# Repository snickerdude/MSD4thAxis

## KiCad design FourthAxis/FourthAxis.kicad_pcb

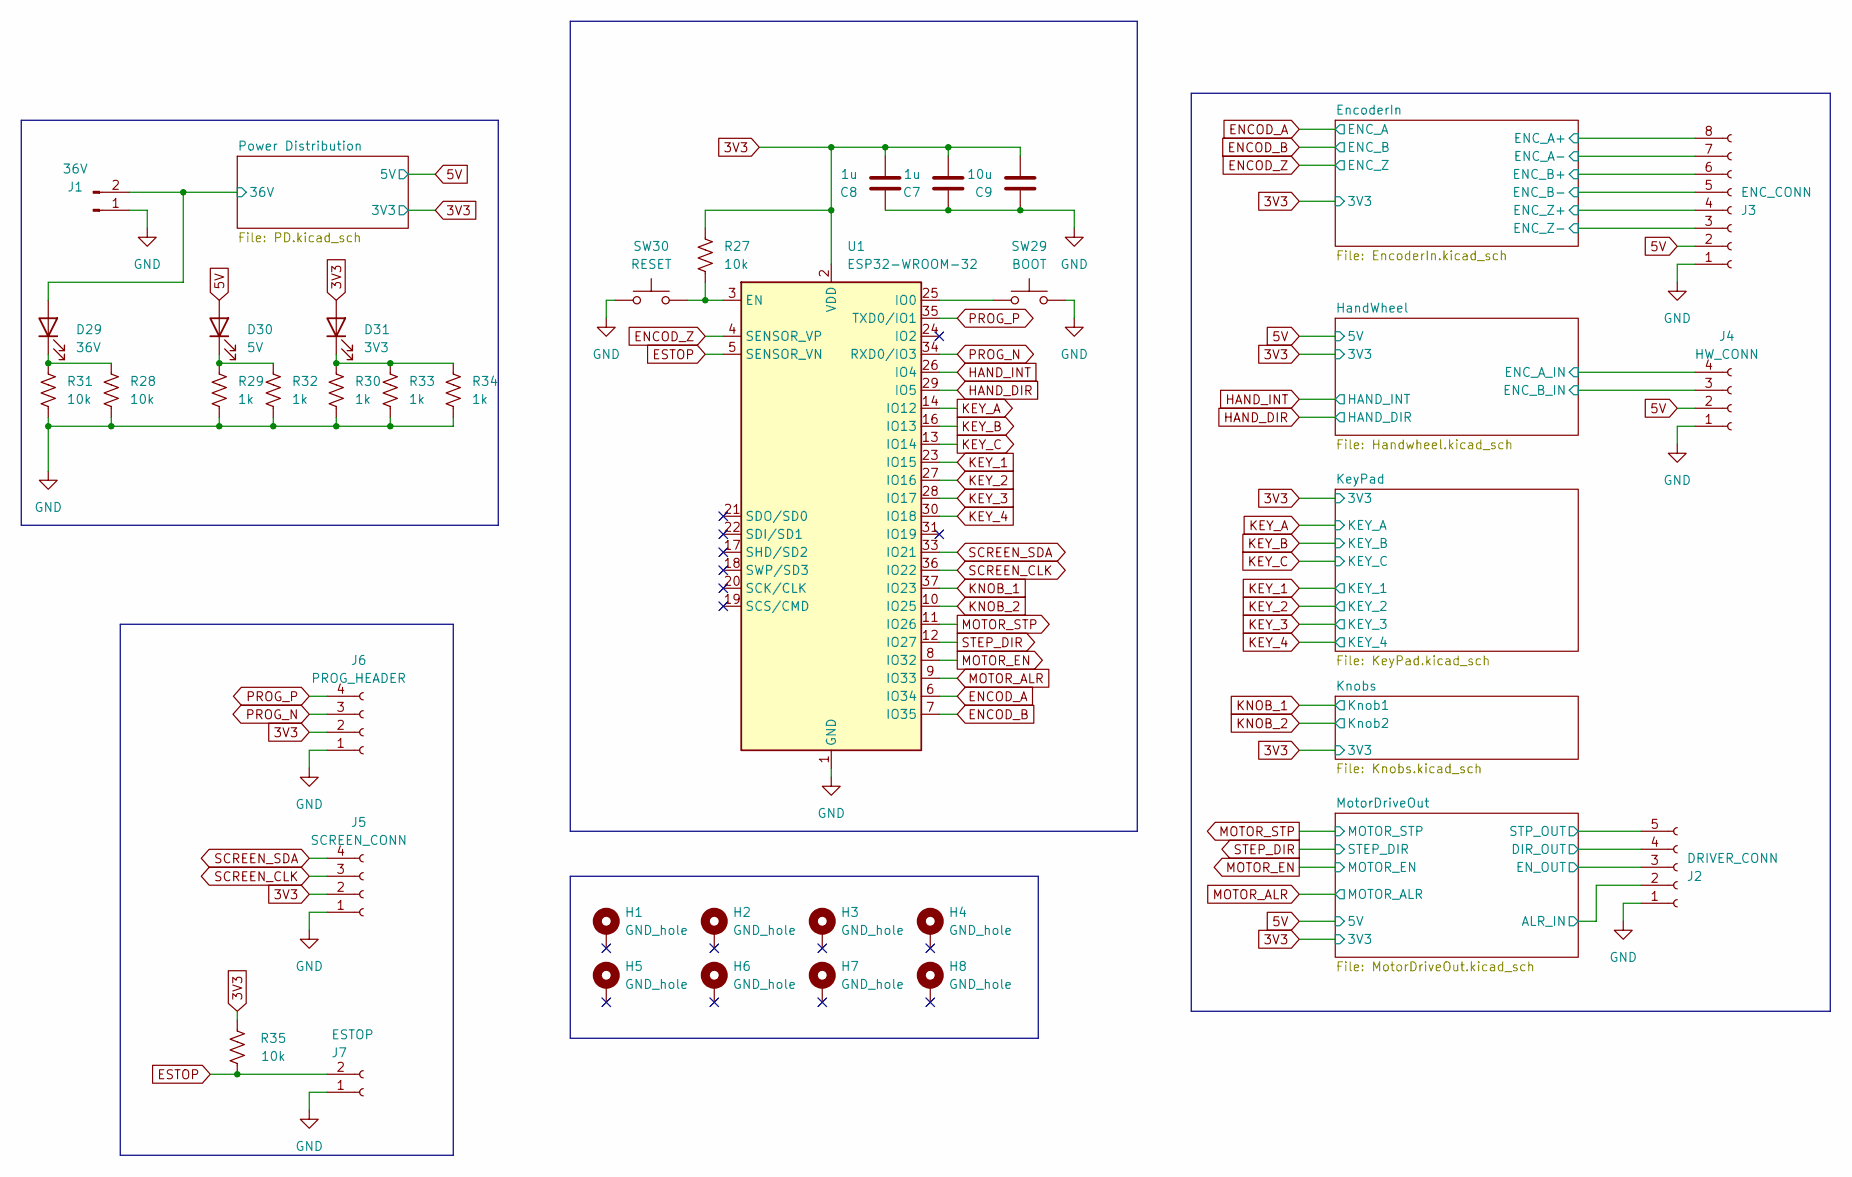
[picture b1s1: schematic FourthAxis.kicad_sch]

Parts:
C7, C8: 1u; C_0603_1608Metric; digikey 1276-1184-1-ND
C9: 10u; C_0603_1608Metric; digikey 1292-0603X106M100CT-ND
D29: 36V; LED_0603_1608Metric; digikey 160-1182-1-ND
D30: 5V; LED_0603_1608Metric; digikey 160-1182-1-ND
D31: 3V3; LED_0603_1608Metric; digikey 160-1182-1-ND
H1, H2, H3, H4, H5, H6, H7, H8: GND_hole; MountingHole_2.2mm_M2_Pad
J1: 36V; PinHeader_1x02_P2.54mm_Vertical
J2: DRIVER_CONN; PinHeader_1x05_P2.54mm_Vertical
J3: ENC_CONN; PinHeader_1x08_P2.54mm_Vertical
J4: HW_CONN; PinHeader_1x04_P2.54mm_Vertical
J5: SCREEN_CONN; PinHeader_1x04_P2.54mm_Vertical
J6: PROG_HEADER; PinHeader_1x04_P2.54mm_Vertical
J7: ESTOP; PinHeader_1x02_P2.54mm_Vertical
R27, R28, R31, R35: 10k; R_0603_1608Metric; digikey 311-10.0KHRCT-ND
R29, R30, R32, R33, R34: 1k; R_0603_1608Metric; digikey 311-1.00KHRCT-ND
SW29: BOOT; SW_Push_1P1T_NO_CK_KMR2; digikey CKN10284CT-ND
SW30: RESET; SW_Push_1P1T_NO_CK_KMR2; digikey CKN10284CT-ND
U1: ESP32-WROOM-32; Digikey Part Number 1965-ESP32-WROOM-32E-N4CT-ND

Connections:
3V3: C7.2, C8.2, C9.2, D31.2 (A), J5.2, J6.2, R27.1, R35.1, U1.2 (VDD); also elsewhere on the board
5V: D30.2 (A), J3.2, J4.2; also elsewhere on the board
/EncoderIn/ENC_A+: J3.8; also elsewhere on the board
/EncoderIn/ENC_A-: J3.7; also elsewhere on the board
/EncoderIn/ENC_B+: J3.6; also elsewhere on the board
/EncoderIn/ENC_B-: J3.5; also elsewhere on the board
/EncoderIn/ENC_Z+: J3.4; also elsewhere on the board
/EncoderIn/ENC_Z-: J3.3; also elsewhere on the board
/HandWheel/ENC_A_IN: J4.4; also elsewhere on the board
/HandWheel/ENC_B_IN: J4.3; also elsewhere on the board
/MotorDriveOut/ALR_IN: J2.2; also elsewhere on the board
/MotorDriveOut/DIR_OUT: J2.4; also elsewhere on the board
/MotorDriveOut/EN_OUT: J2.3; also elsewhere on the board
/MotorDriveOut/STP_OUT: J2.5; also elsewhere on the board
/Power Distribution/36V: D29.2 (A), J1.2; also elsewhere on the board
ENCOD_A: U1.6 (IO34); also elsewhere on the board
ENCOD_B: U1.7 (IO35); also elsewhere on the board
ENCOD_Z: U1.4 (SENSOR_VP); also elsewhere on the board
ESTOP: J7.2, R35.2, U1.5 (SENSOR_VN)
GND: C7.1, C8.1, C9.1, J1.1, J2.1, J3.1, J4.1, J5.1, J6.1, J7.1, R28.2, R29.2, R30.2, R31.2, R32.2, R33.2, R34.2, SW29.2, SW30.2, U1.1 (GND), U1.15 (GND), U1.38 (GND), U1.39 (GND); also elsewhere on the board
HAND_DIR: U1.29 (IO5); also elsewhere on the board
HAND_INT: U1.26 (IO4); also elsewhere on the board
KEY_1: U1.23 (IO15); also elsewhere on the board
KEY_2: U1.27 (IO16); also elsewhere on the board
KEY_3: U1.28 (IO17); also elsewhere on the board
KEY_4: U1.30 (IO18); also elsewhere on the board
KEY_A: U1.14 (IO12); also elsewhere on the board
KEY_B: U1.16 (IO13); also elsewhere on the board
KEY_C: U1.13 (IO14); also elsewhere on the board
KNOB_1: U1.37 (IO23); also elsewhere on the board
KNOB_2: U1.10 (IO25); also elsewhere on the board
MOTOR_ALR: U1.9 (IO33); also elsewhere on the board
MOTOR_EN: U1.8 (IO32); also elsewhere on the board
MOTOR_STP: U1.11 (IO26); also elsewhere on the board
unnamed: D29.1 (K), R28.1, R31.1
unnamed: D30.1 (K), R29.1, R32.1
unnamed: D31.1 (K), R30.1, R33.1, R34.1
unnamed: R27.2, SW30.1, U1.3 (EN)
unnamed: SW29.1, U1.25 (IO0)
PROG_N: J6.3, U1.34 (RXD0/IO3)
PROG_P: J6.4, U1.35 (TXD0/IO1)
SCREEN_CLK: J5.3, U1.36 (IO22)
SCREEN_SDA: J5.4, U1.33 (IO21)
STEP_DIR: U1.12 (IO27); also elsewhere on the board

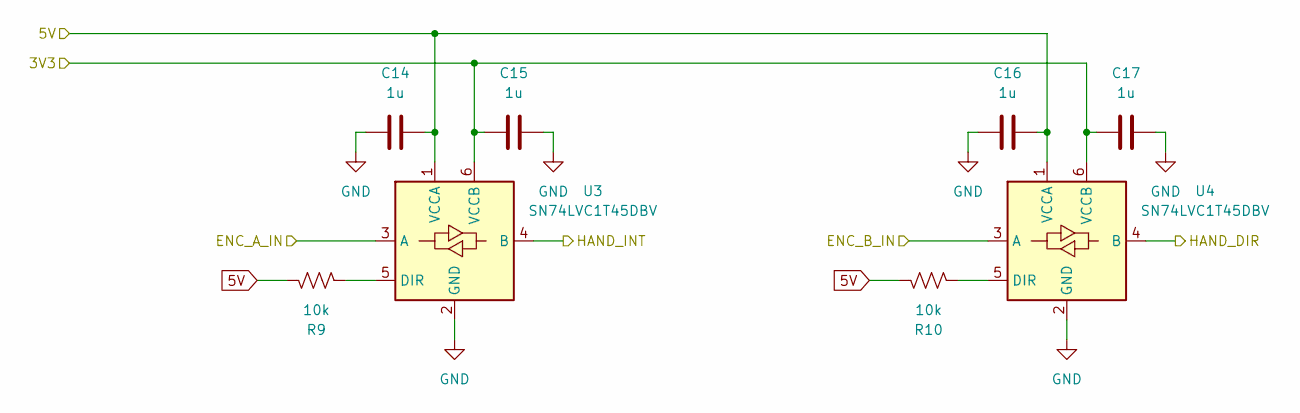
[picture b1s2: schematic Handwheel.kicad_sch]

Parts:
C14, C15, C16, C17: 1u; C_0603_1608Metric; digikey 1276-1184-1-ND
R9, R10: 10k; R_0603_1608Metric; digikey 311-10.0KHRCT-ND
U3, U4: SN74LVC1T45DBV; SOT-23-6; digikey 296-16843-1-ND

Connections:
3V3: C15.2, C17.2, U3.6 (VCCB), U4.6 (VCCB); also elsewhere on the board
5V: C14.1, C16.1, R9.1, R10.1, U3.1 (VCCA), U4.1 (VCCA); also elsewhere on the board
/HandWheel/ENC_A_IN: U3.3 (A); also elsewhere on the board
/HandWheel/ENC_B_IN: U4.3 (A); also elsewhere on the board
GND: C14.2, C15.1, C16.2, C17.1, U3.2 (GND), U4.2 (GND); also elsewhere on the board
HAND_DIR: U4.4 (B); also elsewhere on the board
HAND_INT: U3.4 (B); also elsewhere on the board
unnamed: R9.2, U3.5 (DIR)
unnamed: R10.2, U4.5 (DIR)

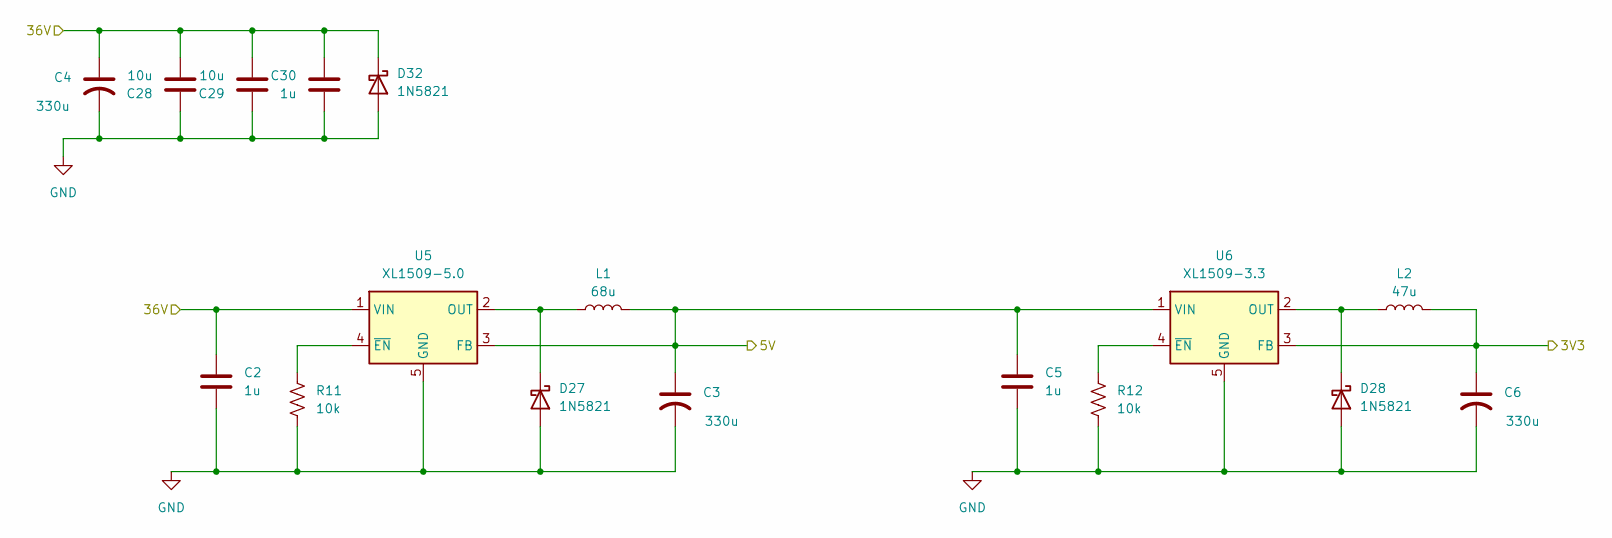
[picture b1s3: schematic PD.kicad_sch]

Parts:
C2, C5, C30: 1u; C_0603_1608Metric; digikey 1276-1184-1-ND
C3, C4, C6: 330u; CP_Elec_6.3x7.7; digikey 493-2157-1-ND
C28, C29: 10u; C_0603_1608Metric; digikey 1292-0603X106M100CT-ND
D27, D28, D32: 1N5821; D_SOD-123; digikey 641-1458-1-ND
L1: 68u; L_12x12mm_H6mm; digikey 399-MPXV1D1250L680CT-ND
L2: 47u; L_12x12mm_H6mm; digikey 399-MPXV1D1250L470CT-ND
R11, R12: 10k; R_0603_1608Metric; digikey 311-10.0KHRCT-ND
U5: XL1509-5.0; SOIC-8_3.9x4.9mm_P1.27mm; digikey 4518-XL1509-5.0CT-ND
U6: XL1509-3.3; SOIC-8_3.9x4.9mm_P1.27mm; digikey 4518-XL1509-3.3CT-ND

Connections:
3V3: C6.1, L2.2, U6.3 (FB); also elsewhere on the board
5V: C3.1, C5.1, L1.2, U5.3 (FB), U6.1 (VIN); also elsewhere on the board
/Power Distribution/36V: C2.1, C4.1, C28.2, C29.2, C30.1, D32.1 (K), U5.1 (VIN); also elsewhere on the board
GND: C2.2, C3.2, C4.2, C5.2, C6.2, C28.1, C29.1, C30.2, D27.2 (A), D28.2 (A), D32.2 (A), R11.2, R12.2, U5.5 (GND), U5.6 (GND), U5.7 (GND), U5.8 (GND), U6.5 (GND), U6.6 (GND), U6.7 (GND), U6.8 (GND); also elsewhere on the board
unnamed: D27.1 (K), L1.1, U5.2 (OUT)
unnamed: D28.1 (K), L2.1, U6.2 (OUT)
unnamed: R11.1, U5.4 (~EN)
unnamed: R12.1, U6.4 (~EN)

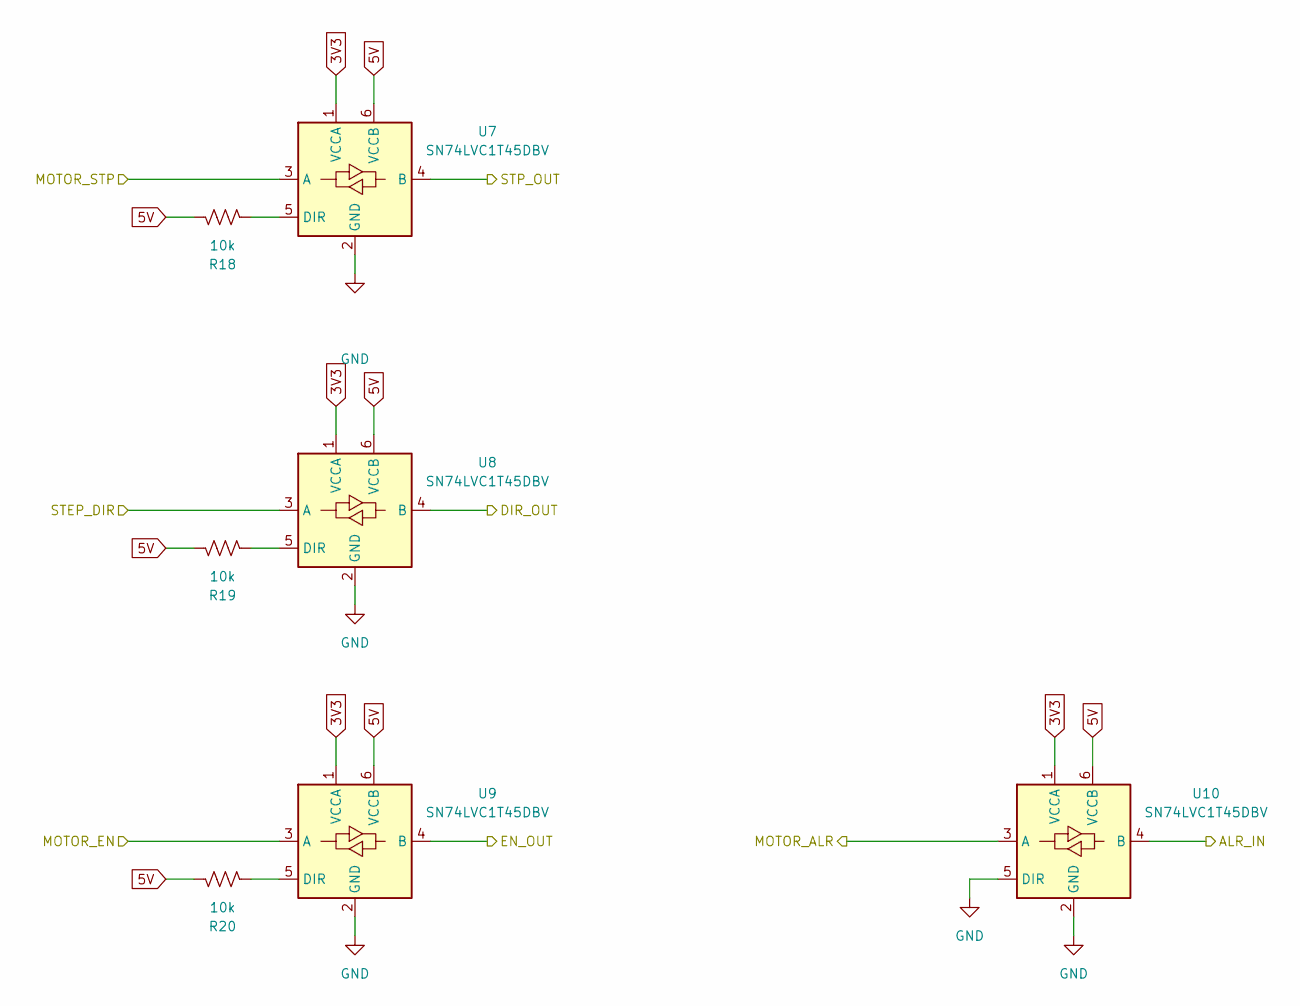
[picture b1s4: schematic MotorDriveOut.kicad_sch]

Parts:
R18, R19, R20: 10k; R_0603_1608Metric; digikey 311-10.0KHRCT-ND
U7, U8, U9, U10: SN74LVC1T45DBV; SOT-23-6; Digikey 74LVC1T45W6-7DICT-ND

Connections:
3V3: U7.1 (VCCA), U8.1 (VCCA), U9.1 (VCCA), U10.1 (VCCA); also elsewhere on the board
5V: R18.1, R19.1, R20.1, U7.6 (VCCB), U8.6 (VCCB), U9.6 (VCCB), U10.6 (VCCB); also elsewhere on the board
/MotorDriveOut/ALR_IN: U10.4 (B); also elsewhere on the board
/MotorDriveOut/DIR_OUT: U8.4 (B); also elsewhere on the board
/MotorDriveOut/EN_OUT: U9.4 (B); also elsewhere on the board
/MotorDriveOut/STP_OUT: U7.4 (B); also elsewhere on the board
GND: U7.2 (GND), U8.2 (GND), U9.2 (GND), U10.2 (GND), U10.5 (DIR); also elsewhere on the board
MOTOR_ALR: U10.3 (A); also elsewhere on the board
MOTOR_EN: U9.3 (A); also elsewhere on the board
MOTOR_STP: U7.3 (A); also elsewhere on the board
unnamed: R18.2, U7.5 (DIR)
unnamed: R19.2, U8.5 (DIR)
unnamed: R20.2, U9.5 (DIR)
STEP_DIR: U8.3 (A); also elsewhere on the board

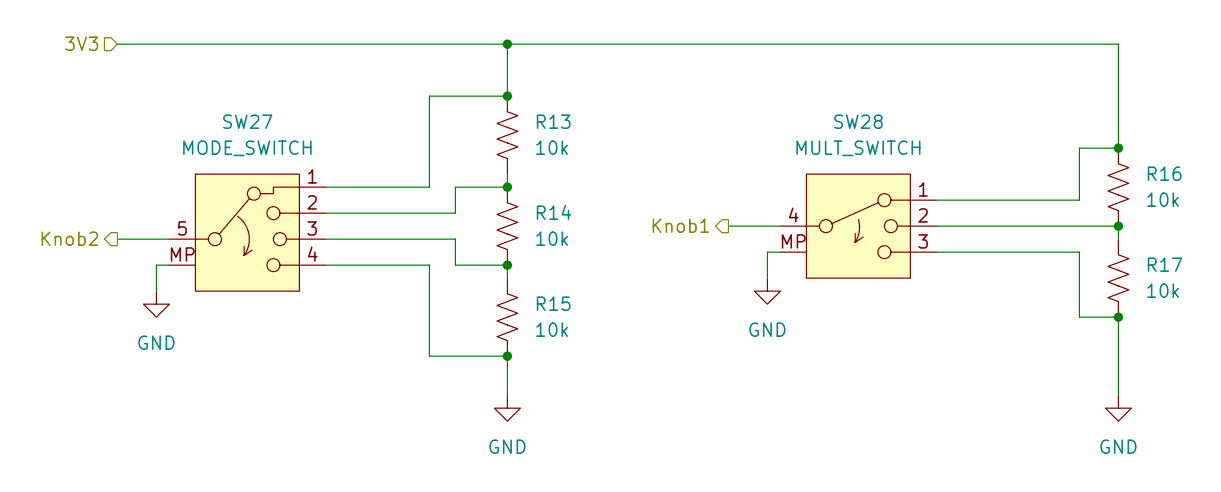
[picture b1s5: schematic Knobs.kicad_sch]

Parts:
R13, R14, R15, R16, R17: 10k; R_0603_1608Metric; digikey 311-10.0KHRCT-ND
SW27: MODE_SWITCH; PinHeader_1x05_P2.54mm_Vertical
SW28: MULT_SWITCH; PinHeader_1x04_P2.54mm_Vertical

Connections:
3V3: R13.1, R16.1, SW27.1, SW28.1; also elsewhere on the board
GND: R15.2, R17.2, SW27.4, SW27.MP, SW28.3, SW28.MP; also elsewhere on the board
KNOB_1: SW28.4; also elsewhere on the board
KNOB_2: SW27.5; also elsewhere on the board
unnamed: R13.2, R14.1, SW27.2
unnamed: R14.2, R15.1, SW27.3
unnamed: R16.2, R17.1, SW28.2

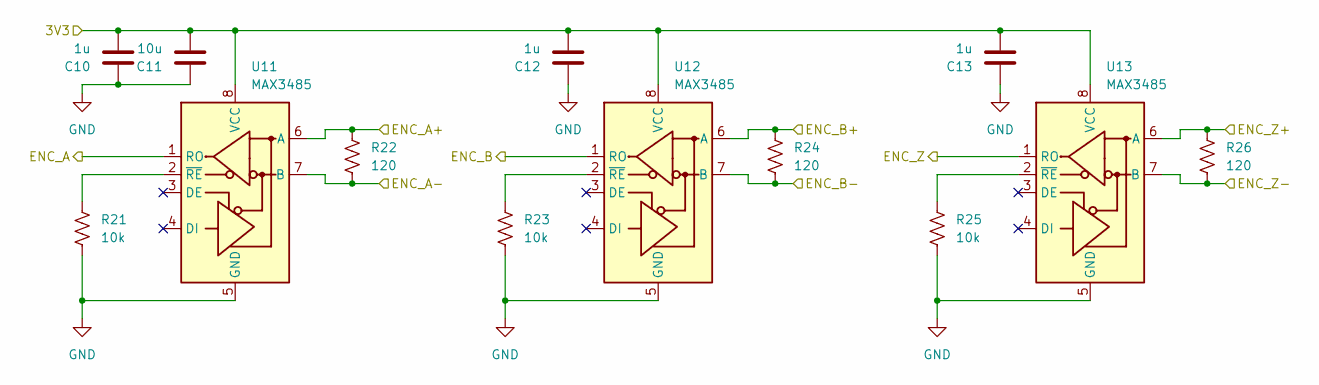
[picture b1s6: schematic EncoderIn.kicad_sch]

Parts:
C10, C12, C13: 1u; C_0603_1608Metric; digikey 1276-1184-1-ND
C11: 10u; C_0603_1608Metric; digikey 1292-0603X106M100CT-ND
R21, R23, R25: 10k; R_0603_1608Metric; digikey 311-10.0KHRCT-ND
R22, R24, R26: 120; R_0603_1608Metric; digikey 541-10426-1-ND
U11, U12, U13: MAX3485; SOIC-8_3.9x4.9mm_P1.27mm; digikey 5272-MAX3485ESA-EVCT-ND

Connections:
3V3: C10.2, C11.2, C12.2, C13.2, U11.8 (VCC), U12.8 (VCC), U13.8 (VCC); also elsewhere on the board
/EncoderIn/ENC_A+: R22.2, U11.6 (A); also elsewhere on the board
/EncoderIn/ENC_A-: R22.1, U11.7 (B); also elsewhere on the board
/EncoderIn/ENC_B+: R24.2, U12.6 (A); also elsewhere on the board
/EncoderIn/ENC_B-: R24.1, U12.7 (B); also elsewhere on the board
/EncoderIn/ENC_Z+: R26.2, U13.6 (A); also elsewhere on the board
/EncoderIn/ENC_Z-: R26.1, U13.7 (B); also elsewhere on the board
ENCOD_A: U11.1 (RO); also elsewhere on the board
ENCOD_B: U12.1 (RO); also elsewhere on the board
ENCOD_Z: U13.1 (RO); also elsewhere on the board
GND: C10.1, C11.1, C12.1, C13.1, R21.2, R23.2, R25.2, U11.5 (GND), U12.5 (GND), U13.5 (GND); also elsewhere on the board
unnamed: R21.1, U11.2 (~RE)
unnamed: R23.1, U12.2 (~RE)
unnamed: R25.1, U13.2 (~RE)

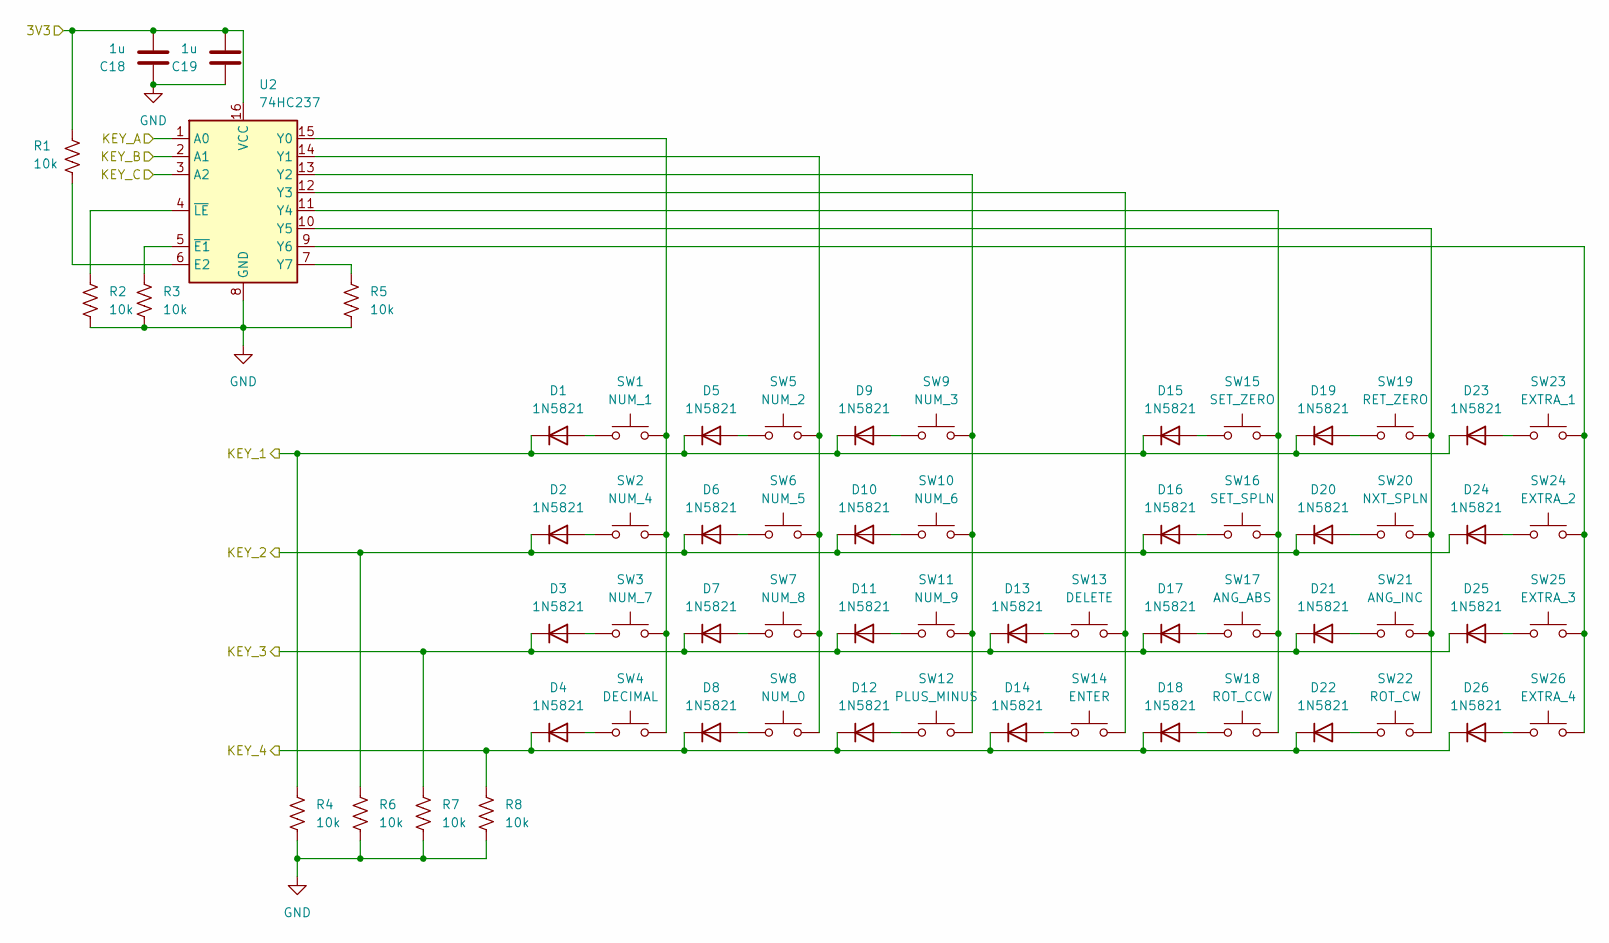
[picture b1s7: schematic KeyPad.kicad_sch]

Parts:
C18, C19: 1u; C_0603_1608Metric; digikey 1276-1184-1-ND
D1, D2, D3, D4, D5, D6, D7, D8, D9, D10, D11, D12, D13, D14, D15, D16, D17, D18, D19, D20, D21, D22, D23, D24, D25, D26: 1N5821; D_SOD-123; digikey 641-1458-1-ND
R1, R2, R3, R4, R5, R6, R7, R8: 10k; R_0603_1608Metric; digikey 311-10.0KHRCT-ND
SW1: NUM_1; SW_Cherry_MX_1.00u_PCB
SW2: NUM_4; SW_Cherry_MX_1.00u_PCB
SW3: NUM_7; SW_Cherry_MX_1.00u_PCB
SW4: DECIMAL; SW_Cherry_MX_1.00u_PCB
SW5: NUM_2; SW_Cherry_MX_1.00u_PCB
SW6: NUM_5; SW_Cherry_MX_1.00u_PCB
SW7: NUM_8; SW_Cherry_MX_1.00u_PCB
SW8: NUM_0; SW_Cherry_MX_1.00u_PCB
SW9: NUM_3; SW_Cherry_MX_1.00u_PCB
SW10: NUM_6; SW_Cherry_MX_1.00u_PCB
SW11: NUM_9; SW_Cherry_MX_1.00u_PCB
SW12: PLUS_MINUS; SW_Cherry_MX_1.00u_PCB
SW13: DELETE; SW_Cherry_MX_1.00u_PCB
SW14: ENTER; SW_Cherry_MX_1.00u_PCB
SW15: SET_ZERO; SW_Cherry_MX_1.00u_PCB
SW16: SET_SPLN; SW_Cherry_MX_1.00u_PCB
SW17: ANG_ABS; SW_Cherry_MX_1.00u_PCB
SW18: ROT_CCW; SW_Cherry_MX_1.00u_PCB
SW19: RET_ZERO; SW_Cherry_MX_1.00u_PCB
SW20: NXT_SPLN; SW_Cherry_MX_1.00u_PCB
SW21: ANG_INC; SW_Cherry_MX_1.00u_PCB
SW22: ROT_CW; SW_Cherry_MX_1.00u_PCB
SW23: EXTRA_1; SW_Cherry_MX_1.00u_PCB
SW24: EXTRA_2; SW_Cherry_MX_1.00u_PCB
SW25: EXTRA_3; SW_Cherry_MX_1.00u_PCB
SW26: EXTRA_4; SW_Cherry_MX_1.00u_PCB
U2: 74HC237; SOIC-16_3.9x9.9mm_P1.27mm; Digikey Part Number 74HC237DCT-ND

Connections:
3V3: C18.2, C19.2, R1.1, U2.16 (VCC); also elsewhere on the board
GND: C18.1, C19.1, R2.2, R3.2, R4.2, R5.2, R6.2, R7.2, R8.2, U2.8 (GND); also elsewhere on the board
KEY_1: D1.1 (K), D5.1 (K), D9.1 (K), D15.1 (K), D19.1 (K), D23.1 (K), R4.1; also elsewhere on the board
KEY_2: D2.1 (K), D6.1 (K), D10.1 (K), D16.1 (K), D20.1 (K), D24.1 (K), R6.1; also elsewhere on the board
KEY_3: D3.1 (K), D7.1 (K), D11.1 (K), D13.1 (K), D17.1 (K), D21.1 (K), D25.1 (K), R7.1; also elsewhere on the board
KEY_4: D4.1 (K), D8.1 (K), D12.1 (K), D14.1 (K), D18.1 (K), D22.1 (K), D26.1 (K), R8.1; also elsewhere on the board
KEY_A: U2.1 (A0); also elsewhere on the board
KEY_B: U2.2 (A1); also elsewhere on the board
KEY_C: U2.3 (A2); also elsewhere on the board
unnamed: D1.2 (A), SW1.1
unnamed: D2.2 (A), SW2.1
unnamed: D3.2 (A), SW3.1
unnamed: D4.2 (A), SW4.1
unnamed: D5.2 (A), SW5.1
unnamed: D6.2 (A), SW6.1
unnamed: D7.2 (A), SW7.1
unnamed: D8.2 (A), SW8.1
unnamed: D9.2 (A), SW9.1
unnamed: D10.2 (A), SW10.1
unnamed: D11.2 (A), SW11.1
unnamed: D12.2 (A), SW12.1
unnamed: D13.2 (A), SW13.1
unnamed: D14.2 (A), SW14.1
unnamed: D15.2 (A), SW15.1
unnamed: D16.2 (A), SW16.1
unnamed: D17.2 (A), SW17.1
unnamed: D18.2 (A), SW18.1
unnamed: D19.2 (A), SW19.1
unnamed: D20.2 (A), SW20.1
unnamed: D21.2 (A), SW21.1
unnamed: D22.2 (A), SW22.1
unnamed: D23.2 (A), SW23.1
unnamed: D24.2 (A), SW24.1
unnamed: D25.2 (A), SW25.1
unnamed: D26.2 (A), SW26.1
unnamed: R1.2, U2.6 (E2)
unnamed: SW1.2, SW2.2, SW3.2, SW4.2, U2.15 (Y0)
unnamed: SW5.2, SW6.2, SW7.2, SW8.2, U2.14 (Y1)
unnamed: SW9.2, SW10.2, SW11.2, SW12.2, U2.13 (Y2)
unnamed: SW13.2, SW14.2, U2.12 (Y3)
unnamed: SW15.2, SW16.2, SW17.2, SW18.2, U2.11 (Y4)
unnamed: SW19.2, SW20.2, SW21.2, SW22.2, U2.10 (Y5)
unnamed: SW23.2, SW24.2, SW25.2, SW26.2, U2.9 (Y6)
unnamed: R5.1, U2.7 (Y7)
unnamed: R3.1, U2.5 (~E1)
unnamed: R2.1, U2.4 (~LE)

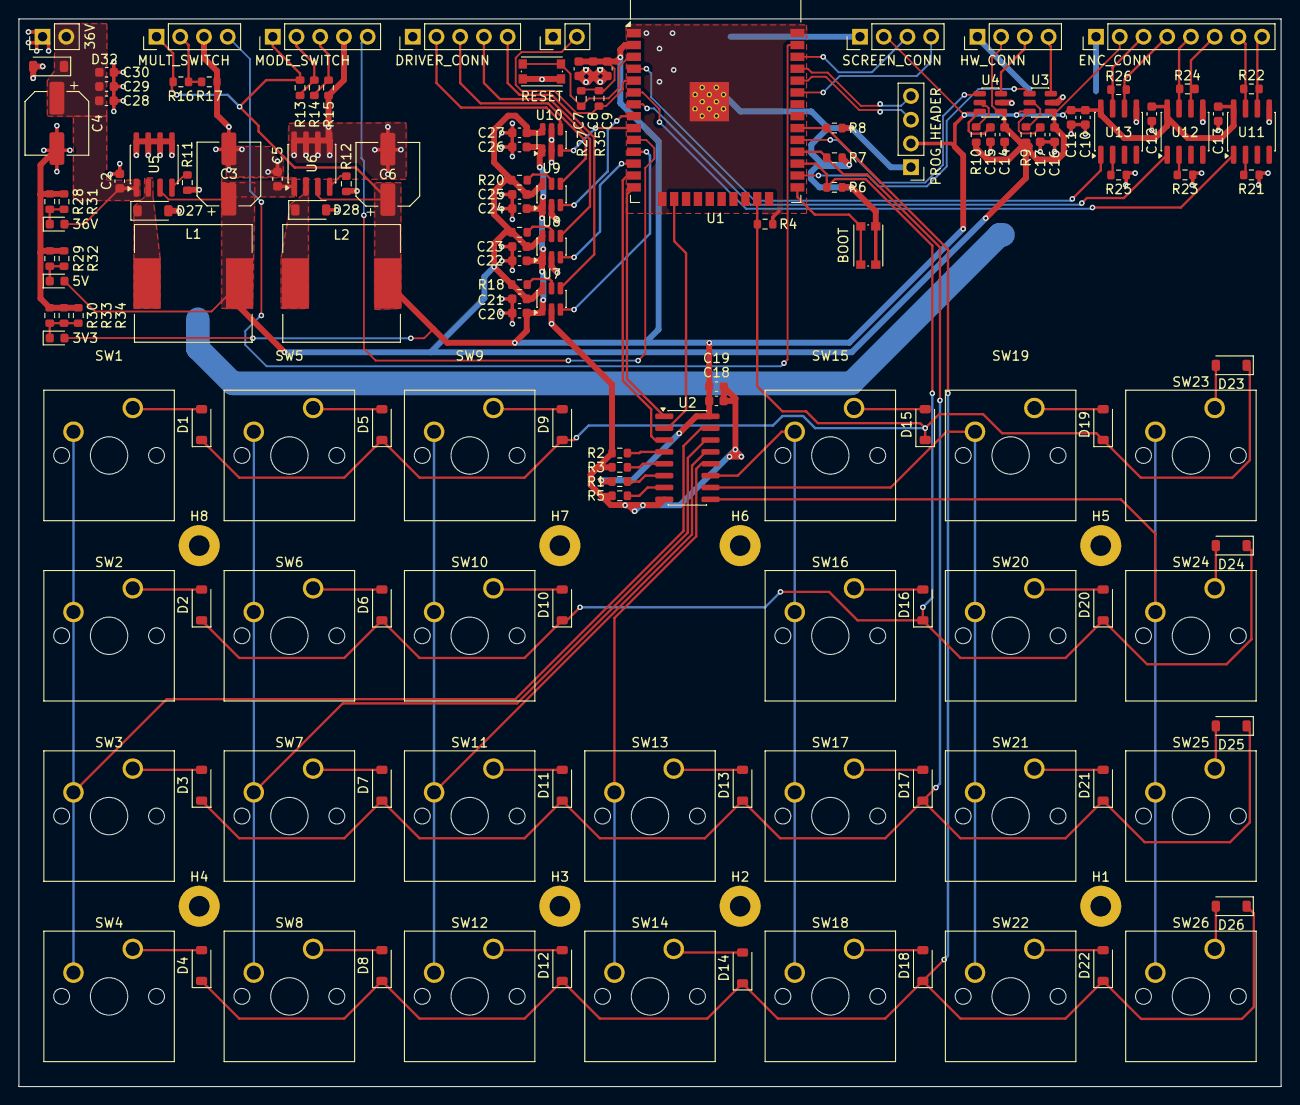
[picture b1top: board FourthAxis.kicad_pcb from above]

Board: 2 copper layers, 135.1 x 114.3 mm, 156 parts (0 on the bottom side), 96 nets.

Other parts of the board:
C20, C21, C22, C23, C24, C25, C26, C27: 1u; C_0603_1608Metric

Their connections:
3V3: C20.1, C22.1, C24.1, C26.1; also elsewhere on the board
5V: C21.2, C23.2, C25.2, C27.2; also elsewhere on the board
GND: C20.2, C21.1, C22.2, C23.1, C24.2, C25.1, C26.2, C27.1; also elsewhere on the board

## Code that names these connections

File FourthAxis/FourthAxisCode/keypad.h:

//#pragma once

#ifndef KEYPAD_H
#define KEYPAD_H

#include <Arduino.h>
#include <vector>

//key constants
enum KeyCode : uint8_t {
    K_NONE = 0,
    K_DECIMAL = '.',
    K_PLUSMINUS = '~',      // any unused printable/nonprintable value works
    K_DEL = 0x80,
    K_ENTER,
    K_SET_ZERO,
    K_RETURN_ZERO,
    K_SET_SPLINES,
    K_NEXT_ANGLE,
    K_SET_ANGLE_ABS,
    K_ADD_ANGLE_INC,
    K_JOG_CCW,
    K_JOG_CW
};

class keypad {
public:
	// Class constructor
    keypad();
	// Class destructor
	~keypad();
	
	/**
	 * @brief Initialize the GPIO pins. Call this in setup().
	 */
	void begin();

	/**
	 * @brief Periodic scan of the matrix. Call this in loop().
	 * This is non-blocking and handles debouncing internally.
	 */
	void update();

	/**
	 * @brief Scan all the keys and serial print which ones are pressed
	 */
	void scan();

	/**
	 * @brief Register a callback function for key events.
	 */
	//void registerCallback(KeyCallback callback);

	/**
	 * @brief Check if a specific key is currently pressed (active state).
	 */
	bool isKeyPressed(uint8_t key) const;
	uint8_t getKey();                 // returns a newly pressed key once, else K_NONE

private:
const uint8_t* _keyMap;
uint8_t _lastPressed = K_NONE;

private:
	
	// Pin definitions for the 8 MUXed cols and the 4 rows.
	static const uint8_t KEY_A = 	12;
	static const uint8_t KEY_B = 	13;
	static const uint8_t KEY_C = 	14;
	static const uint8_t KEY_1 = 	15;	
	static const uint8_t KEY_2 = 	16;
	static const uint8_t KEY_3 = 	17;
	static const uint8_t KEY_4 = 	18;
	
	// Number of rows and columns in the keyboard
	static const uint8_t NUM_ROWS =	4;
	static const uint8_t NUM_COLS =	7;
	
	// GPIO mask used to clear the MUX outputs
	static const uint32_t CLR_MASK =	0x00007000;
	// GPIO mask used to read the keeb inputs
	static const uint32_t READ_MASK =	0x00078000;
	
	
    

	// Internal tracking structures
	bool* _keyStates;       // Current stable debounced state of each key
	bool* _rawStates;       // Raw physical state during scan
	unsigned long* _lastDebounceTime; // Timestamp of last state flip per key

	static constexpr unsigned long DEBOUNCE_DELAY_MS = 25; // Debounce window
	//KeyCallback _eventCallback = nullptr;

	// Helper to translate 2D coordinates to a flat index
	inline int getIndex(uint8_t row, uint8_t col) const {
			return (row * NUM_COLS) + col;
	}
};

#endif // MCP3562_H

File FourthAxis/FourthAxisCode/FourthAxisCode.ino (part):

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//1:100 worm gear ratio so 20000
#define STEPS_PER_REV (MOTOR_STEPS*WORM_REDUC)
// pins used for the stepper driver
#define MOTOR_STP 26
#define MOTOR_DIR 27
#define MOTOR_EN 32
// target position of the motor in steps
// signed integer so it can rotate backwards
int32_t TARGET_POS = 0;
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#define KNOB_MODE 25 //knob 2

// pins used for the stepper driver
#define MOTOR_STP 26
#define MOTOR_DIR 27
#define MOTOR_EN 32

//pin for ESTOP
#define ESTOP 39

// function prototypes
void StepperOutTask(void* params);
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  kp.begin();
  
  pinMode(MOTOR_DIR, OUTPUT);
  pinMode(MOTOR_STP, OUTPUT);
  pinMode(MOTOR_EN, OUTPUT);

  xTaskCreatePinnedToCore(
    StepperOutTask, /* Function to implement the task */
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
  POS_mutex = xSemaphoreCreateMutex();

  pinMode(ESTOP, INPUT);
  pinMode(KNOB_MULT, INPUT);
  pinMode(KNOB_MODE, INPUT);
  digitalWrite(MOTOR_DIR, HIGH);
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
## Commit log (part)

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2026-03-25 initial ESP32 pinout
2026-03-26 Laptop close
2026-03-30 test
2026-04-01 Progress save
2026-04-01 Added handwheel sheet
2026-04-01 test'
2026-04-01 today
2026-04-01 upgraded
2026-04-02 Added PD sheet
2026-04-02 Added PD symbols
2026-04-06 Keypad schem work
2026-04-06 footprints
2026-04-06 fixing commit
2026-04-06 key model added
2026-04-06 schem changes
2026-04-07 started handwheel
2026-04-08 schem additions
2026-04-08 name and layout
2026-04-08 Shaun work
2026-04-08 shaun today
2026-04-08 Nick end of wed
2026-04-08 shaun add
2026-04-13 Name changes
2026-04-13 Encoder input added?
2026-04-13 shaunmotorwork
2026-04-15 shaunconnectors
2026-04-20 digikey PN and footprints
2026-04-22 Layout work
2026-05-06 syncing
2026-05-16 Layout work, added power LEDs
2026-05-29 started routing
2026-05-30 traces almost complete
2026-06-01 done?
2026-06-06 Generated Fab Files
2026-06-06 BOM export
2026-06-23 boards ordered
